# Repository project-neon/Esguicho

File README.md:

# Esguicho

## Arquivos

  Neste repositório temos os principais arquivos que usamos para os 3 capítulos, Eletrônica, Mecânica e Software. Segue abaixo uma lista do que temos em cada uma das pastas:

  ### Electronics
    Na parte eletrônica, utilizamos o programa Kicad que é open source e permite a criação e edição de PCBs.
    Caso queira editar ou vizualizar o projeto, clone o diretório "Eletronics", pois nele está contido o esquemático 
    no formato PDF e sch,  a PCB no formato pcb e os arquivos pro e plr próprios do Kicad.
    
  ### Mechanics
    Na pasta da mecânica, há arquivos no formato step e stl para que possam ser utilizados para visualização 
    e manufatura 3D, juntamente com os arquivos pdf dos desenhos técnicos para melhor compreensão do projeto
    
  ### Software
    Nesta pasta deixamos todos os arquivos que formam o código do robô. Então .ino e .h são os principais arquivos.
    Usamos os .h's para segmentar o código e não ser um único bloco enorme, dividindo eles de acordo com sua funcionalidade.
    O .ino é onde fica a base de todo o código, como o setup() e o loop(). Temos os códigos de testes e o código autonomous
    que usamos durante as lutas oficiais.

## Fluxo Git
- Quando for acrescentar uma feature (um comportamento novo para o robô), crie uma brancha chamada `feat/nome-da-feature`
- Quando for corrir algum bug no código, crie uma brancha chamada `fix/nome-do-fix`
- Quando for adicionar novos arquivos na mecância ou eletrônica, crie uma brancha chamada `update/eletronics-<data>` ou `update/mechanis-<data>`, exemplo: `update/eletronics-01-04-2023`
- A partir da main: `git checkout -b nome-da-branch`, ex: `git checkout -b feat/novos-testes`

## Na hora de fazer o commit
- Nomeie o seu commit primeiro dizendo o que foi feito, ex: `fix: `, `feat: ` ou `update: `
- Você pode adicionar no assunto (comentário) ou na mensagem do commit também onde que a mudança foi feita.
- `git push`

Para saber mais de commits, você pode acessar esse [link](https://www.freecodecamp.org/news/how-to-write-better-git-commit-messages/)

## Na hora de fazer o merge
- Depois de subir o commit, crie um PR (Pull Request) e peça pro resto do pessoal da equipe dar uma conferida antes de ser aprovado

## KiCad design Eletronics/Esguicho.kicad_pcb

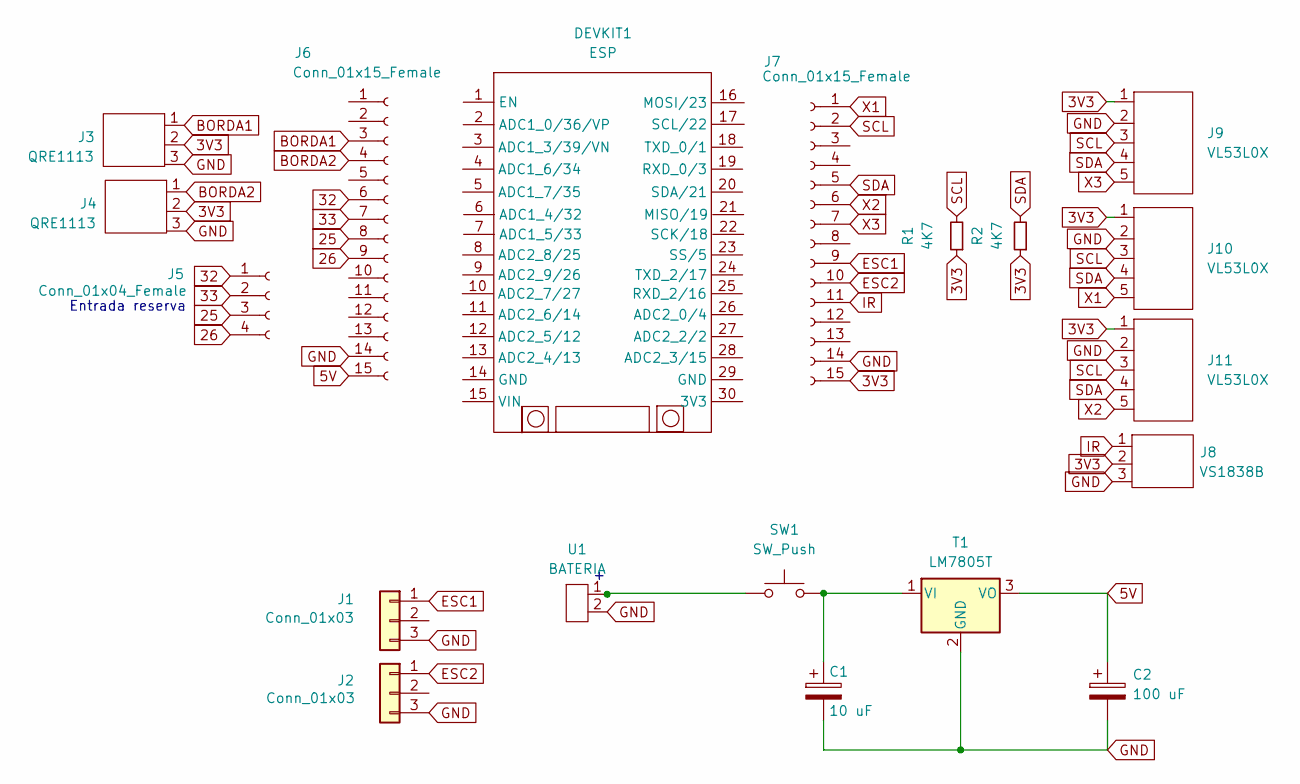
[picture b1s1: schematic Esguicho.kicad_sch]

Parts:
C1: 10 uF; CP_Radial_D5.0mm_P2.50mm
C2: 100 uF; CP_Radial_D6.3mm_P2.50mm
DEVKIT1: ESP
J1, J2: Conn_01x03; JST_XH_S3B-XH-A_1x03_P2.50mm_Horizontal
J3, J4: QRE1113; JST_XH_S3B-XH-A_1x03_P2.50mm_Horizontal
J5: Conn_01x04_Female; PinSocket_1x04_P2.54mm_Vertical
J6, J7: Conn_01x15_Female; PinSocket_1x15_P2.54mm_Vertical
J8: VS1838B; JST_XH_S3B-XH-A_1x03_P2.50mm_Horizontal
J9, J10, J11: VL53L0X; JST_XH_S5B-XH-A_1x05_P2.50mm_Horizontal
R1, R2: 4K7; R_Axial_DIN0207_L6.3mm_D2.5mm_P10.16mm_Horizontal
SW1: SW_Push; Nidec_Copal_SH-7010C
T1: LM7805T; TO-220-3_Vertical
U1: BATERIA; JST_XH_S2B-XH-A_1x02_P2.50mm_Horizontal

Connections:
3V3: J3.2, J4.2, J7.15, J8.2, J9.1, J10.1, J11.1, R1.1, R2.1
5V: C2.1, J6.15, T1.3 (VO)
25: J5.3, J6.8
26: J5.4, J6.9
32: J5.1, J6.6
33: J5.2, J6.7
BORDA1: J3.1, J6.3
BORDA2: J4.1, J6.4
ESC1: J1.1, J7.9
ESC2: J2.1, J7.10
GND: C1.2, C2.2, J1.3, J2.3, J3.3, J4.3, J6.14, J7.14, J8.3, J9.2, J10.2, J11.2, T1.2 (GND), U1.2
IR: J7.11, J8.1
unnamed: C1.1, SW1.2, T1.1 (VI)
unnamed: SW1.1, U1.1
SCL: J7.2, J9.3, J10.3, J11.3, R1.2
SDA: J7.5, J9.4, J10.4, J11.4, R2.2
X1: J7.1, J10.5
X2: J7.6, J11.5
X3: J7.7, J9.5

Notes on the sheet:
Entrada reserva

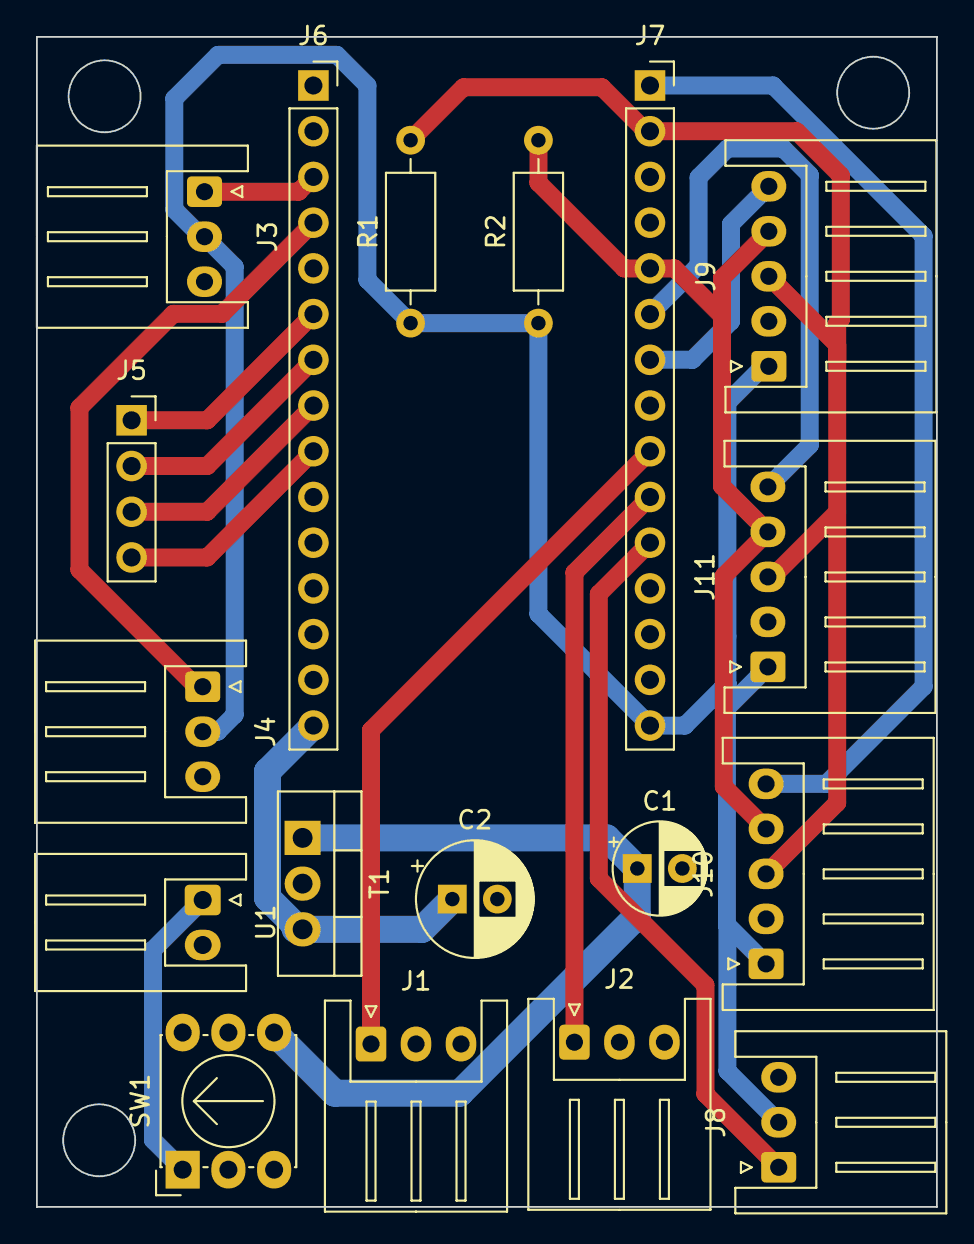
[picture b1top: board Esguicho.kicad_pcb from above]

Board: 2 copper layers, 50.0 x 65.0 mm, 18 parts (0 on the bottom side), 19 nets.

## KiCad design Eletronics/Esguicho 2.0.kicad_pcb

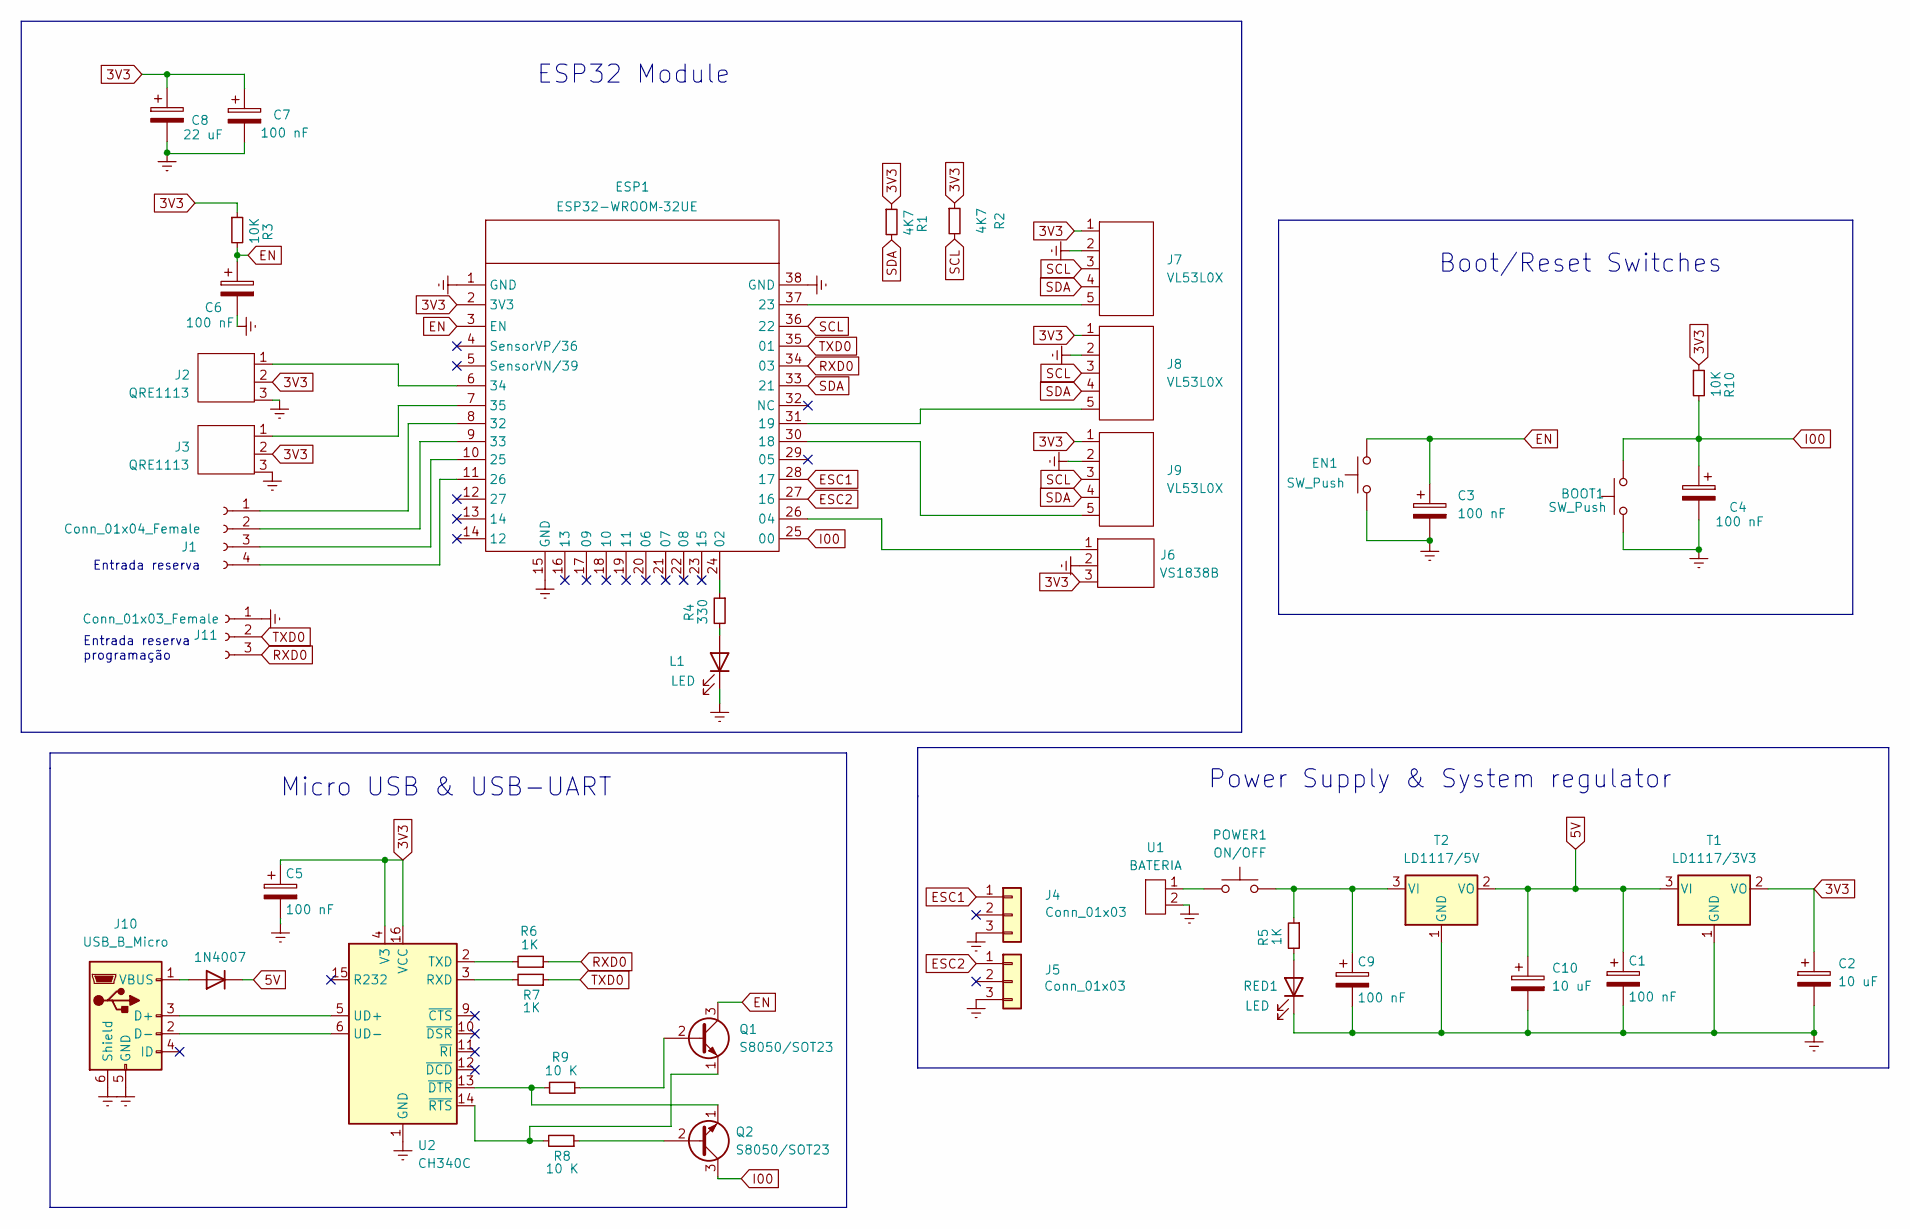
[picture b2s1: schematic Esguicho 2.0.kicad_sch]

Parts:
BOOT1: SW_Push; SW_SPST_TL3305A
C1, C3, C4, C5, C6, C7, C9: 100 nF; C_0603_1608Metric
C2, C10: 10 uF; C_0603_1608Metric
C8: 22 uF; C_0603_1608Metric
D1: 1N4007; D_SMA
EN1: SW_Push; SW_SPST_TL3305A
ESP1: ESP32-WROOM­32UE; ESP32-WROOM-32
J1: Conn_01x04_Female; PinSocket_1x04_P2.54mm_Vertical
J2, J3: QRE1113; JST_PH_S3B-PH-K_1x03_P2.00mm_Horizontal
J4, J5: Conn_01x03; JST_XH_B3B-XH-AM_1x03_P2.50mm_Vertical
J6: VS1838B; JST_ZE_B03B-ZESK-1D_1x03_P1.50mm_Vertical
J7, J8, J9: VL53L0X; JST_PH_S5B-PH-K_1x05_P2.00mm_Horizontal
J10: USB_B_Micro; USB_Micro-B_Amphenol_10118194_Horizontal
J11: Conn_01x03_Female; PinSocket_1x03_P2.54mm_Vertical
L1: LED; LED_0603_1608Metric
POWER1: ON/OFF; Nidec_Copal_SH-7010C
Q1, Q2: S8050/SOT23; SOT-23
R1, R2: 4K7; R_0603_1608Metric
R3, R10: 10K; R_0603_1608Metric
R4: 330; R_0603_1608Metric
R5, R6, R7: 1K; R_0603_1608Metric
R8, R9: 10 K; R_0603_1608Metric
RED1: LED; LED_0603_1608Metric
T1: LD1117/3V3; SOT-223-3_TabPin2
T2: LD1117/5V; SOT-223-3_TabPin2
U1: BATERIA; JST_XH_B2B-XH-AM_1x02_P2.50mm_Vertical
U2: CH340C; SOIC-16_3.9x9.9mm_P1.27mm

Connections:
3V3: C2.1, C5.1, C7.1, C8.1, ESP1.2 (3V3), J2.2, J3.2, J6.3, J7.1, J8.1, J9.1, R1.1, R2.1, R3.1, R10.1, T1.2 (VO), U2.4 (V3), U2.16 (VCC)
5V: C1.1, C10.1, D1.1 (K), T1.3 (VI), T2.2 (VO)
EN: C3.1, C6.1, EN1.1, ESP1.3 (EN), Q1.3 (C), R3.2
ESC1: ESP1.28 (17), J4.1
ESC2: ESP1.27 (16), J5.1
GNDREF: BOOT1.2, C1.2, C2.2, C3.2, C4.2, C5.2, C6.2, C7.2, C8.2, C9.2, C10.2, EN1.2, ESP1.1 (GND), ESP1.15 (GND), ESP1.38 (GND), J2.3, J3.3, J4.3, J5.3, J6.2, J7.2, J8.2, J9.2, J10.5 (GND), J10.6 (Shield), J11.1, L1.1 (K), RED1.1 (K), T1.1 (GND), T2.1 (GND), U1.2, U2.1 (GND)
I00: BOOT1.1, C4.1, ESP1.25 (00), Q2.3 (C), R10.2
unnamed: C9.1, POWER1.2, POWER1.8, R5.1, T2.3 (VI)
unnamed: D1.2 (A), J10.1 (VBUS)
unnamed: ESP1.6 (34), J2.1
unnamed: ESP1.7 (35), J3.1
unnamed: ESP1.8 (32), J1.1
unnamed: ESP1.9 (33), J1.2
unnamed: ESP1.10 (25), J1.3
unnamed: ESP1.11 (26), J1.4
unnamed: ESP1.24 (02), R4.1
unnamed: ESP1.26 (04), J6.1
unnamed: ESP1.30 (18), J9.5
unnamed: ESP1.31 (19), J8.5
unnamed: ESP1.37 (23), J7.5
unnamed: J10.2 (D-), U2.6 (UD-)
unnamed: J10.3 (D+), U2.5 (UD+)
unnamed: L1.2 (A), R4.2
unnamed: POWER1.1, POWER1.4, U1.1
unnamed: Q1.1 (E), R8.2, U2.14 (~RTS)
unnamed: Q1.2 (B), R9.1
unnamed: Q2.1 (E), R9.2, U2.13 (~DTR)
unnamed: Q2.2 (B), R8.1
unnamed: R5.2, RED1.2 (A)
unnamed: R6.2, U2.2 (TXD)
unnamed: R7.2, U2.3 (RXD)
RXD0: ESP1.34 (03), J11.3, R6.1
SCL: ESP1.36 (22), J7.3, J8.3, J9.3, R2.2
SDA: ESP1.33 (21), J7.4, J8.4, J9.4, R1.2
TXD0: ESP1.35 (01), J11.2, R7.1

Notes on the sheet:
Entrada reserva
Micro USB & USB-UART
Boot/Reset Switches
Entrada reserva programação
ESP32 Module
Power Supply & System regulator

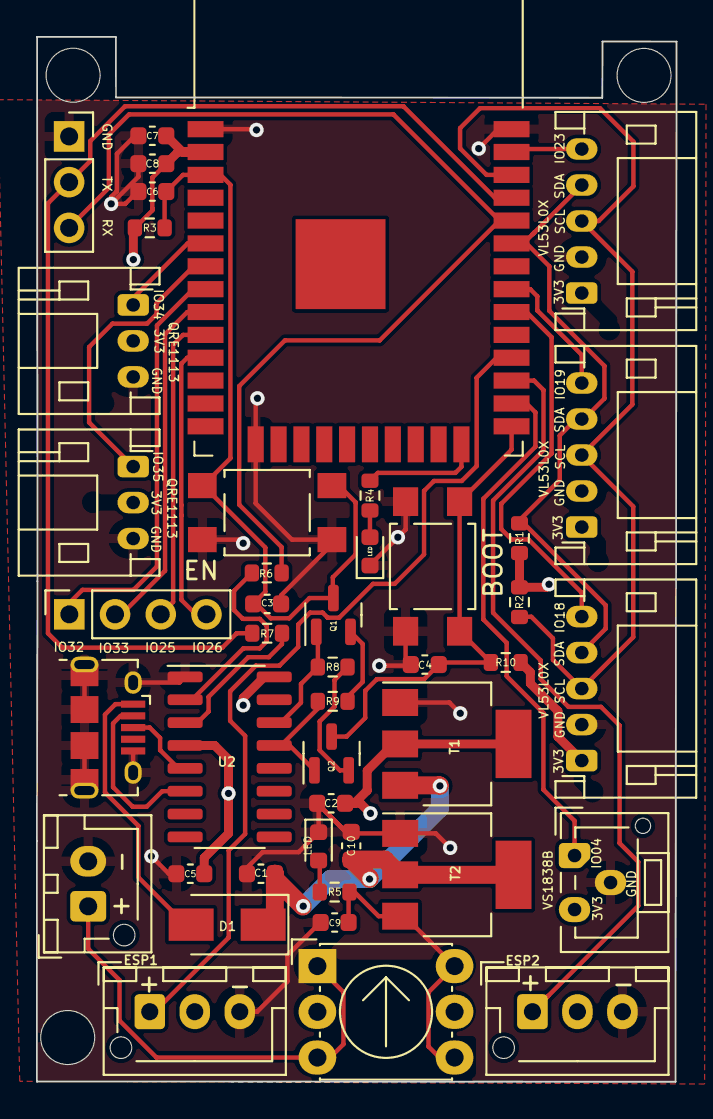
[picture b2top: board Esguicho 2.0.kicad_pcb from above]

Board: 2 copper layers, 35.5 x 58.0 mm, 45 parts (1 on the bottom side), 35 nets.

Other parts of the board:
G: LOGO; Logo.Neon

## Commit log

2022-09-07 feat: Cronograma das tarefas
2022-09-07 feat: Esguicho's pinouts (autonomous and remote)
2022-09-21 feat: tests archives
2022-09-21 Starting the main code
    - Por enquanto, estou deixando simples, então nós não recebemos os comandos do controle do Juiz e qual estratégia que o robô vai usar é escrita dentro do código
    - Comecei a lógica de escolhe de estratégia, separando a estratégia do loop e fazendo um Switch Case
2022-09-26 feat: adding MeiaLua strategies
2022-10-01 fix: mudança do nome.ino para alinhar com o nome da pasta
2022-10-01 fix: remoção do arquivo com nome incongruente à pasta
2022-10-01 fix: nomenclaturas
2022-10-01 feat: Edge sensors test
2022-10-01 fix: edge sensors test
2022-10-01 feat: IR tests
2022-10-08 fix: organização e padronização estrategias
2022-10-08 fix: variavel de controle da vel geral
2022-10-12 fix: teste IRremote funcionando
2022-10-12 fix: changing timer++ for millis()
2022-10-12 feat: teste juiz
2022-10-12 feat: codigo teste sensores de distancia
2022-10-13 feat: simple tests
2022-10-14 feat: código base, estrategia simples
2022-10-15 feat: led pisca quando aperta 1
2022-10-20 código usado na ironcup após primeiro dia
2022-11-10 add: lib versions
2022-11-10 Closing Version - Fechamento de Versão
2023-01-10 feat: controller address Ana fix: simplifying code
2023-01-11 feat: breaking the code into smaller pieces
2023-01-13 update: terminando de organizar o codigo
2023-01-16 fix: atualizações pós teste
2023-01-18 feat: teste de tracao
2023-01-18 feat: teste tracao 2 + novos valores controle IR Ana
2023-01-20 feat: novos testes
2023-02-04 Teste Commit conta Leticia
2023-02-04 fix: valor inicia ESC, Vel Max, mudanca brupta vel
2023-02-04 teste
2023-02-04 fix: halllelujah
2023-02-11 feat: teste geral para os motores
2023-02-11 remocao de testes de motores redundantes
2023-02-23 add: teste para a inspecao
2023-02-24 fix: teste de inspecao pos teste
2023-02-24 add: simplifica codigo parar robo antes de girar
2023-02-25 SIMPLIFICAO do codigo para a competicao
2023-03-18 fix: cleaning code for Pull Request
2023-03-18 fix: cleaning all trash code we don't use anymore
2023-03-18 change: chaging files place - Software
2023-03-18 deleting: chaging files place - Software
2023-03-18 add: Eletronics files
2023-03-20 add: info about each folder on README
2023-03-25 fix: organizing the code and chang PT to EN
2023-03-26 fix: Standard Strategy
2023-04-05 Add: Test Led-Blink Nesteru
2023-04-07 fix: _config.h name to only config.h
2023-04-07 fix: 3 strategies code - simple, 3Sensores, Standard
2023-04-08 fix: IRremote v3
2023-04-08 fix: distance read and pint 3Sensors Strategy
2023-05-18 /feat: RC scrípts great work by @AleFukamati
2023-05-26 fix: refinando o controle
2023-05-26 fix: Electronics file name
2023-05-26 fix: IR sensor to Continuos mode update: Constants values, add: Middle Sensor
2024-03-05 fix: update IR lib to work with the judge controller
2025-02-12 chore: change code for new PCB
